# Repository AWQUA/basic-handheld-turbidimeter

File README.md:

#Basic Handheld Turbidimeter
##Purpose  
The Basic Handheld Turbidimeter is designed to measure turbidity on demand, portably, for the lowest possible price.  

##Function  
_How does the device measure a parameter?_  
This device is a single-beam [nephelometrer](https://en.wikipedia.org/wiki/Nephelometer). Light from an infrared light-emitting diode (IR LED) is scattered by suspended sediment as it passes through a sample of water. This scattered light is detected by an IR-sensitive [photodiode](https://en.wikipedia.org/wiki/Photodiode) mounted at a right angle to the center of the IR LED's light beam. The intensity of light detected by the photodiode is referenced to a calibration curve stored in the device's memory to interpolate the corresponding turbidity value, measured in [nephelometric turbidity units (NTU)](http://or.water.usgs.gov/grapher/fnu.html).  

_How does the device record data?_  
This device is intended for basic manual operation and does not contain storage for data.   

_How does the device display data?_  
The microcontroller at the heart of this device reads the frequency of pulses transmitted by the [photodiode unit](http://www.mouser.com/ProductDetail/ams/TSL230BRD-TR/?qs=sGAEpiMZZMu97qiQi8P%252buifvOPr%252b402N67DKHn09PFo%3d), interpolates the turbidity value from stored calibration data, and displays the turbidity value on a [four-digit display panel](http://www.electrodragon.com/product/7-segment-4-digit-display-common-anode/) (much like those used in some alarm clocks).

_What units does the device report in?_  
Like all AWQUA turbidimeters, this device reports readings in  [nephelometric turbidity units (NTU)](http://or.water.usgs.gov/grapher/fnu.html).  

_How does the device communicate data electronically?_  
This device does not possess data telemetry capabilities.  

##Use Case  
_Where can the device be safely used?_  
This device can handle temperatures up to 70C, and is intended for field conditions. It is not water proof or water resistent, however.

##Power  
_How is the device powered?_  
This device uses 3.3V DC power, and requires less than 100mA of current. A standard 3.7V lithium ion or polymer battery, or three AA alkaline batteries, would suffice to power it.

_How much power does it use?_  
In semi-automated testing, this device was capable of taking 5000 measurements on one set of three AA batteries.

##Standard and Testing  
_How was the device tested?_  
Testing procedures for this device are described in full in [An Affordable Open-Source Turbidimeter](http://www.mdpi.com/1424-8220/14/4/7142).

_How did it perform?_  
Testing results for this device are described in full in [An Affordable Open-Source Turbidimeter](http://www.mdpi.com/1424-8220/14/4/7142). The figure below shows the performance of this model of device, versus a popular commercial turbidimeter.  

_What performance standards does the device meet?_  
This device was designed and successfully tested to reliably measure turbidity values well below 1.0 NTU, which is the maximum turbidity value recommended by the World Health Organization for drinking water prior to disinfection. Please note however that this device is not certified to meet EPA requirements for the routine turbidity monitoring of treated drinking water in the United States. 

_What monitoring standards can this device be used to meet?_  
This device is one of several proven turbidimeter designs out there that can be used to meet international and World Health Organization guidelines on turbidity monitoring, yet are not able to meet the very exacting (and expensive) American and European turbidity detection standards. There is an urgent global need for simple, affordable turbidity detection, and AWQUA members are working to establish alternative turbidity detection standards to address this need. Please check out our [Standards](https://github.com/AWQUA/Standards) repository for more information.

##Construction  

###Bill of Materials
| Quantity  | Part Description | Example Price (each) |
| :-------------: | ------------- | :-------------: |
| 1 | ATMega328P-PU microprocessor  | [$2.90](http://www.electrodragon.com/product/atmega328-with-arduino-optiboot-uno/)|
| 1 | 4-digit, 7-segment display  | [$2.10](http://www.electrodragon.com/product/7-segment-4-digit-display-common-anode/)|
| 1 | 74HC595 shift register  | [$0.62](http://www.mouser.com/ProductDetail/Texas-Instruments/SN74HC595N/?qs=sGAEpiMZZMuyBeSSR239IeaeNSzgQbS%2f1btldJdqa6k%3d) |
| 1 | LMT86 temperature sensor  | [$1.00](http://www.mouser.com/ProductDetail/Texas-Instruments/LMT86LP/?qs=sGAEpiMZZMvfFCidbTccA1jyVRrxk5nB%252bTEjPRynSGM%3d)|
| 1 | TSL230BRD  | [$4.83](http://www.mouser.com/ProductDetail/ams/TSL230BRD-TR/?qs=sGAEpiMZZMu97qiQi8P%252buifvOPr%252b402N67DKHn09PFo%3d)|
| 1 | LF33ABV 3.3V Voltage regulator  | [$1.03](http://www.mouser.com/ProductDetail/STMicroelectronics/LF33ABV/?qs=sGAEpiMZZMsGz1a6aV8DcBQiArhhid1gDswAeAw%2fIB0%3d)|
| 2 | 10uF aluminum electrolytic capacitors  | [$0.24](http://www.mouser.com/ProductDetail/Nichicon/ULD1J100MDD1TD/?qs=sGAEpiMZZMvwFf0viD3Y3c1N%2fF%2fpDmX12XlNW9X9Y3vZmYyMo5GpOw%3d%3d)|
| 2 | 22pF ceramic capacitors  | [$0.03](http://www.mouser.com/ProductDetail/Vishay-BC-Components/K220J10C0GF5UH5/?qs=sGAEpiMZZMsh%252b1woXyUXj9nJp%252b8gphztXIKBUu3gv%252bs%3d)|
| 5 | 100nF ceramic capacitors  | [$0.06](http://www.mouser.com/ProductDetail/Vishay-BC-Components/K104Z15Y5VE5TL2/?qs=sGAEpiMZZMsh%252b1woXyUXj5VNmf0jXPWIrWjnp1zAXac%3d)|
| 4 | 100 ohm resistors  | [$0.10](http://www.mouser.com/ProductDetail/KOA-Speer/MOS1-2CT52R101J/?qs=sGAEpiMZZMtlubZbdhIBICYVxaT5CDYBpEIIN%2f0BoAk%3d)|
| 1 | 220 ohm resistors  | [$0.10](http://www.mouser.com/ProductDetail/KOA-Speer/MOS1-2CT52R221J/?qs=sGAEpiMZZMtlubZbdhIBICYVxaT5CDYBStqm8FrIljg%3d)|
| 1 | 1K ohm resistors 1% tolerance | [$0.10](http://www.mouser.com/ProductDetail/Vishay-Beyschlag/MBB02070C1001FCT00/?qs=sGAEpiMZZMtlubZbdhIBIAA6NYEPHyksoxlYyK2s%252btM%3d)|
| 4 | 10K ohm resistors  | [$0.10](http://www.mouser.com/ProductDetail/Vishay-Beyschlag/MBA02040C1002FCT00/?qs=sGAEpiMZZMtlubZbdhIBIP7908E9uONJr6Tgqqo7oLA%3d)|
| 1 | IR LED  | [$0.47](http://www.mouser.com/ProductDetail/Kingbright/WP7113SF4C/?qs=sGAEpiMZZMvAL21a%2fDhxMro1KOf4QOs%252bCw5JRgjZK8o%3d)|
| 1 | LED lighting driver | [$0.54](http://www.mouser.com/Search/ProductDetail.aspx?R=AL5809-30S1-7virtualkey62110000virtualkey621-AL5809-30S1-7)|
| 1 | Momentary contact button  | [$0.91](http://www.mouser.com/ProductDetail/Mountain-Switch/104-0013-EVX/?qs=sGAEpiMZZMvxtGF7dlGNpr35VnaTB25ys95hy84%252ba4o%3d)|
| 1 | SPST power switch  | [$1.15](http://www.mouser.com/ProductDetail/CHERRY/TRG22F2FBBNN/?qs=sGAEpiMZZMtNT9UGfLL4eOd3cDQgL8vM5i2VNLX9H3E%3d)|
| 100 | Header pins (0.1" spacing)  | [$.00225](http://www.electrodragon.com/product/break-away-header/)|
|||
||**Total Cost:**|**$17.61**|
###Circuit Board
####Schematic

####Layout

###Assembly
For assembly instructions, see the [Supplementary Materials](http://www.mdpi.com/1424-8220/14/4/7142/s1) for An Affordable Open-Source Turbidimeter.  
##FAQ and Troubleshooting  
###Online Resources

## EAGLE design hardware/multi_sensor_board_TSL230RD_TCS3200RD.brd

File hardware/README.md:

#Hardware
There are up to three boards in the `basic-handheld-turbidimeter`: the main board (housing the microprocessor), a sensor board that connects to the main board through 0.1" header pins, and an optional third board that lets the display plug directly in to the main board.

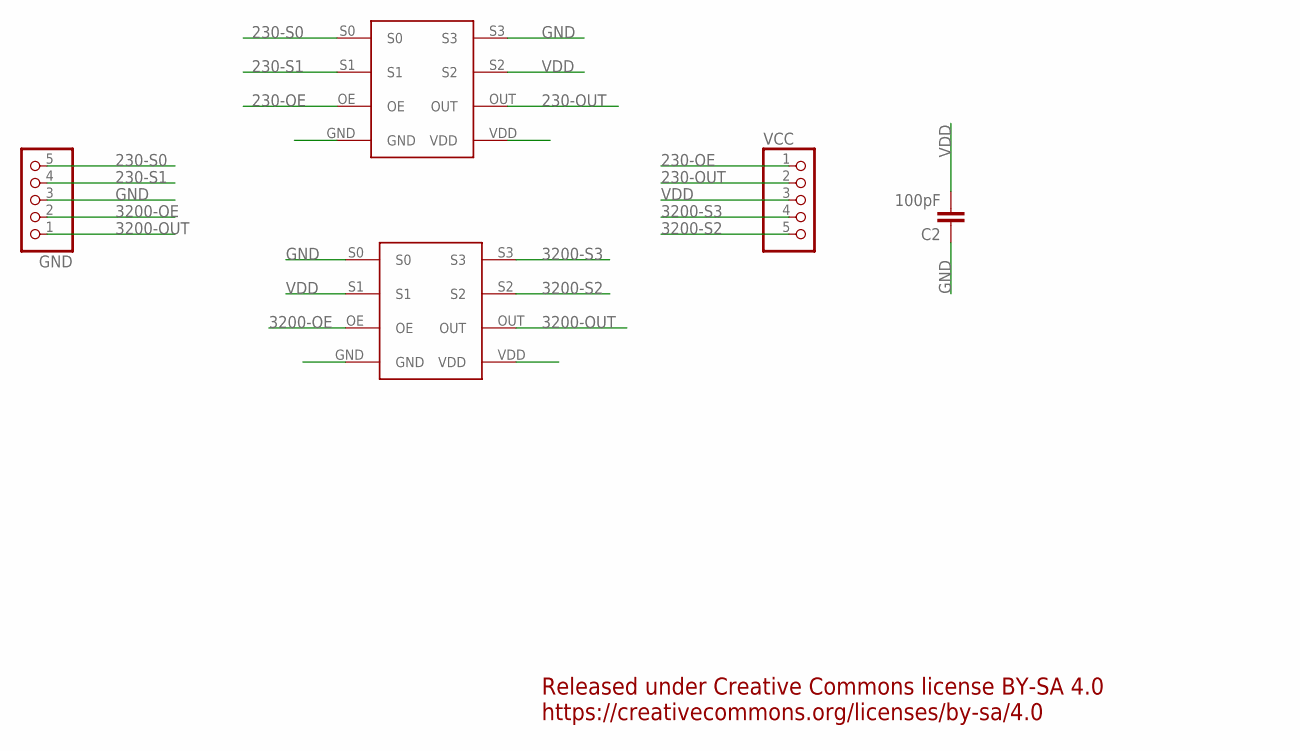
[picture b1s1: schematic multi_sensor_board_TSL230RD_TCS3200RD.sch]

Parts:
C2: 100pF; 0805
COLOR: TCS3200RD; TSL230RD
GND: PINHD-1X5; 1X05
IR: TSL230R; TSL230RD
VCC: PINHD-1X5; 1X05

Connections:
230-OE: IR.OE, VCC.1
230-OUT: IR.OUT, VCC.2
230-S0: GND.5, IR.S0
230-S1: GND.4, IR.S1
3200-OE: COLOR.OE, GND.2
3200-OUT: COLOR.OUT, GND.1
3200-S2: COLOR.S2, VCC.5
3200-S3: COLOR.S3, VCC.4
GND: C2.1, COLOR.GND, COLOR.S0, GND.3, IR.GND, IR.S3
VDD: C2.2, COLOR.S1, COLOR.VDD, IR.S2, IR.VDD, VCC.3

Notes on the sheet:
Released under Creative Commons license BY-SA 4.0 https://creativecommons.org/licenses/by-sa/4.0

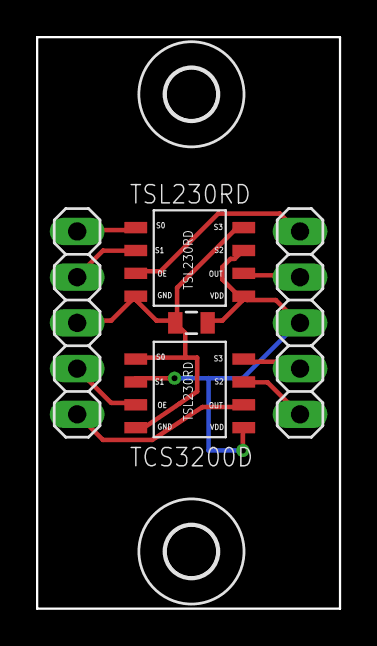
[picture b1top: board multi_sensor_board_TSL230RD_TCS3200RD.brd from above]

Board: 2 copper layers, 16.8 x 31.8 mm, 7 parts (0 on the bottom side), 10 nets.

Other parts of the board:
U$1, U$2: 2,8

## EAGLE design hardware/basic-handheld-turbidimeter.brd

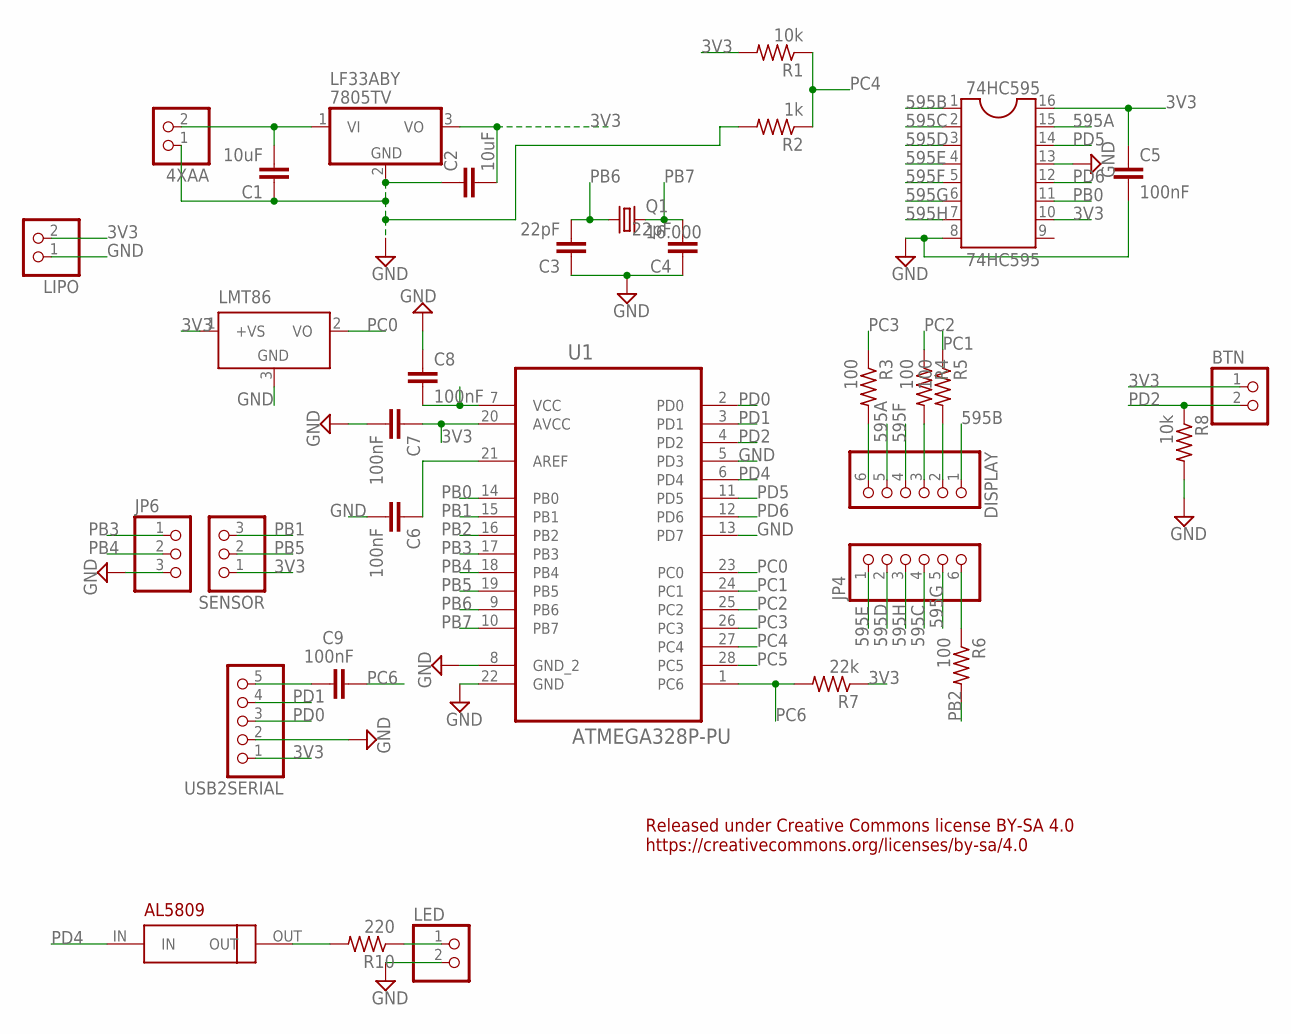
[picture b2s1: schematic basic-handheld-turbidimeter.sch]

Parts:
4XAA: PINHD-1X2; 1X02
74HC595: 74HC595; DIL16
BTN: PINHD-1X2; 1X02
C1, C2: 10uF; CAP-PTH-SMALLEZ
C3, C4: 22pF; CAP-PTH-SMALLEZ
C5, C6, C7, C8, C9: 100nF; CAP-PTH-SMALLEZ
DISPLAY: PINHD-1X6; 1X06
JP4: PINHD-1X6; 1X06
JP6: PINHD-1X3; 1X03
LED: PINHD-1X2; 1X02
LF33ABY: 7805TV; TO220V
LIPO: PINHD-1X2; 1X02
LMT86: LM35CZ; TO92
Q1: 16.000; HC49/S
R1, R8: 10k; 0207/12
R2: 1k; 0207/12
R3, R4, R5, R6: 100; 0207/12
R7: 22k; 0207/12
R10: 220; 0207/12
SENSOR: PINHD-1X3; 1X03
U1: ATMEGA328P-PU; DIP254P762X457-28
U$6: AL5809
USB2SERIAL: PINHD-1X5; 1X05

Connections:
3V3: 74HC595.10, 74HC595.16, BTN.1, C2.2, C5.1, C7.1, C8.2, LF33ABY.3 (VO), LIPO.2, LMT86.1 (+VS), R1.2, R7.1, SENSOR.1, U1.7 (VCC), U1.20 (AVCC), USB2SERIAL.1
595A: 74HC595.15, DISPLAY.5
595B: 74HC595.1, DISPLAY.1
595C: 74HC595.2, JP4.4
595D: 74HC595.3, JP4.2
595E: 74HC595.4, JP4.1
595F: 74HC595.5, DISPLAY.4
595G: 74HC595.6, JP4.5
595H: 74HC595.7, JP4.3
GND: 4XAA.1, 74HC595.8, 74HC595.13, C1.1, C2.1, C3.1, C4.1, C5.2, C6.2, C7.2, C8.1, JP6.3, LED.2, LF33ABY.2 (GND), LIPO.1, LMT86.3 (GND), R2.2, R8.2, U1.5 (PD3), U1.8 (GND_2), U1.13 (PD7), U1.22 (GND), USB2SERIAL.2
LED: LED.1, R10.1
unnamed: 4XAA.2, C1.2, LF33ABY.1 (VI)
unnamed: R10.2, U$6.OUT
unnamed: C6.1, U1.21 (AREF)
unnamed: C9.2, USB2SERIAL.5
unnamed: DISPLAY.6, R3.2
unnamed: DISPLAY.3, R4.2
unnamed: DISPLAY.2, R5.2
unnamed: JP4.6, R6.1
PB0: 74HC595.11, U1.14 (PB0)
PB1: SENSOR.3, U1.15 (PB1)
PB2: R6.2, U1.16 (PB2)
PB3: JP6.1, U1.17 (PB3)
PB4: JP6.2, U1.18 (PB4)
PB5: SENSOR.2, U1.19 (PB5)
PB6: C3.2, Q1.1, U1.9 (PB6)
PB7: C4.2, Q1.2, U1.10 (PB7)
PC0: LMT86.2 (VO), U1.23 (PC0)
PC1: R5.1, U1.24 (PC1)
PC2: R4.1, U1.25 (PC2)
PC3: R3.1, U1.26 (PC3)
PC4: R1.1, R2.1, U1.27 (PC4)
PC5: U1.28 (PC5)
PC6: C9.1, R7.2, U1.1 (PC6)
PD0: U1.2 (PD0), USB2SERIAL.3
PD1: U1.3 (PD1), USB2SERIAL.4
PD2: BTN.2, R8.1, U1.4 (PD2)
PD4: U1.6 (PD4), U$6.IN
PD5: 74HC595.14, U1.11 (PD5)
PD6: 74HC595.12, U1.12 (PD6)

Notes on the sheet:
Released under Creative Commons license BY-SA 4.0 https://creativecommons.org/licenses/by-sa/4.0

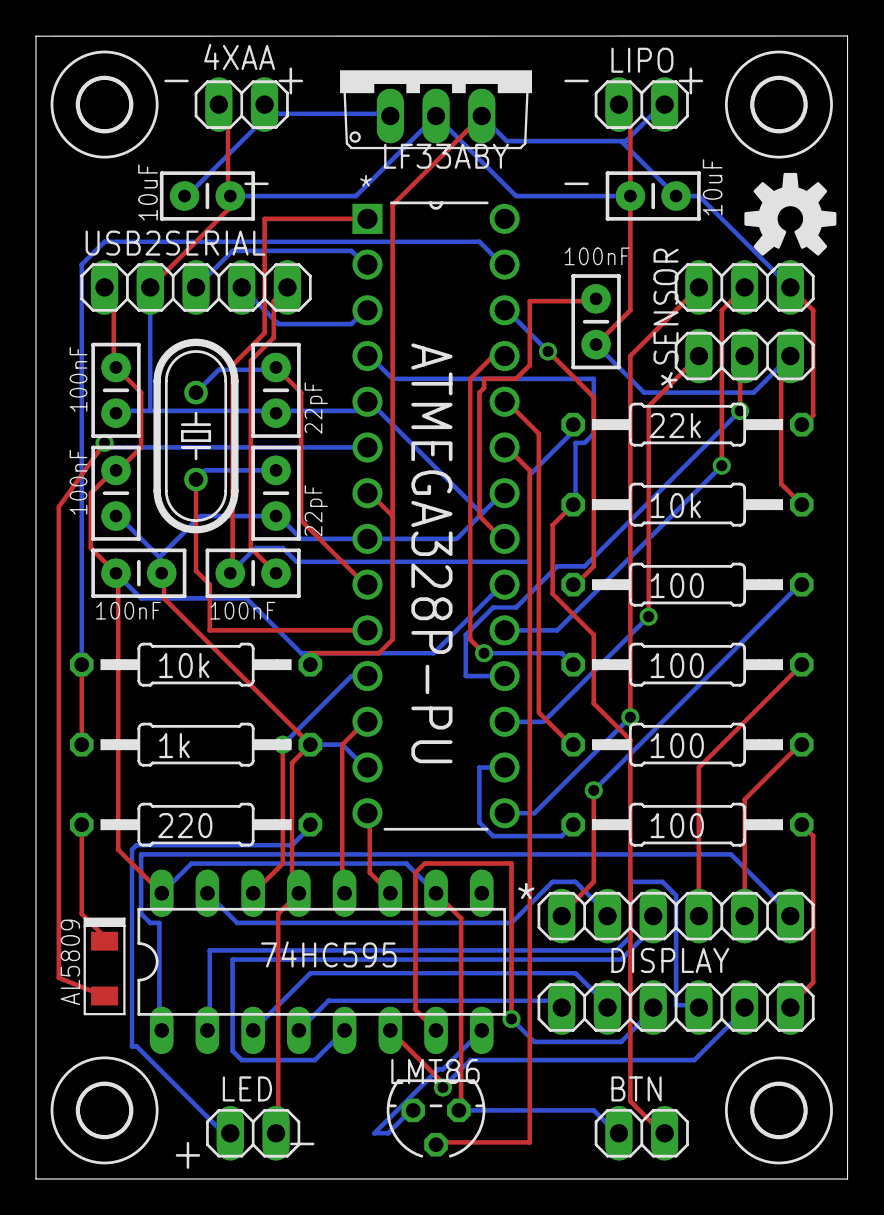
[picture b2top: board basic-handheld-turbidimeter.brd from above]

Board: 2 copper layers, 45.1 x 63.5 mm, 38 parts (0 on the bottom side), 39 nets.

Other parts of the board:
U$1, U$2, U$3, U$4: 2,8
U$5: OSHW-LOGO-M

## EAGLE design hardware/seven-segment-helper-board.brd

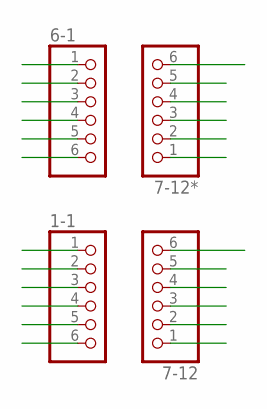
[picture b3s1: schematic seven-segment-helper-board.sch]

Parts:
1-1, 6-1, 7-12, 7-12*: PINHD-1X6; 1X06

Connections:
1: 1-1.1, 6-1.1
2: 1-1.2, 6-1.2
3: 1-1.3, 6-1.3
4: 1-1.4, 6-1.4
5: 1-1.5, 6-1.5
6: 1-1.6, 6-1.6
7: 7-12.1, 7-12*.1
8: 7-12.2, 7-12*.2
9: 7-12.3, 7-12*.3
10: 7-12.4, 7-12*.4
11: 7-12.5, 7-12*.5
12: 7-12.6, 7-12*.6

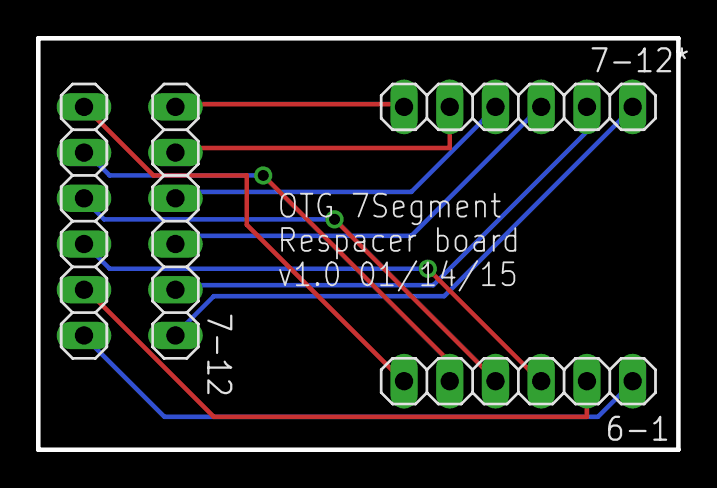
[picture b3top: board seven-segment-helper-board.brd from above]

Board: 2 copper layers, 35.6 x 22.9 mm, 4 parts (0 on the bottom side), 12 nets.

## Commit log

2016-03-27 migrated from AWQUA/Measurement

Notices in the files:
parts and their libraries:
SparkFun-Capacitors: Licensing: CC v3.0 Share-Alike You are welcome to use this library for commercial purposes.
